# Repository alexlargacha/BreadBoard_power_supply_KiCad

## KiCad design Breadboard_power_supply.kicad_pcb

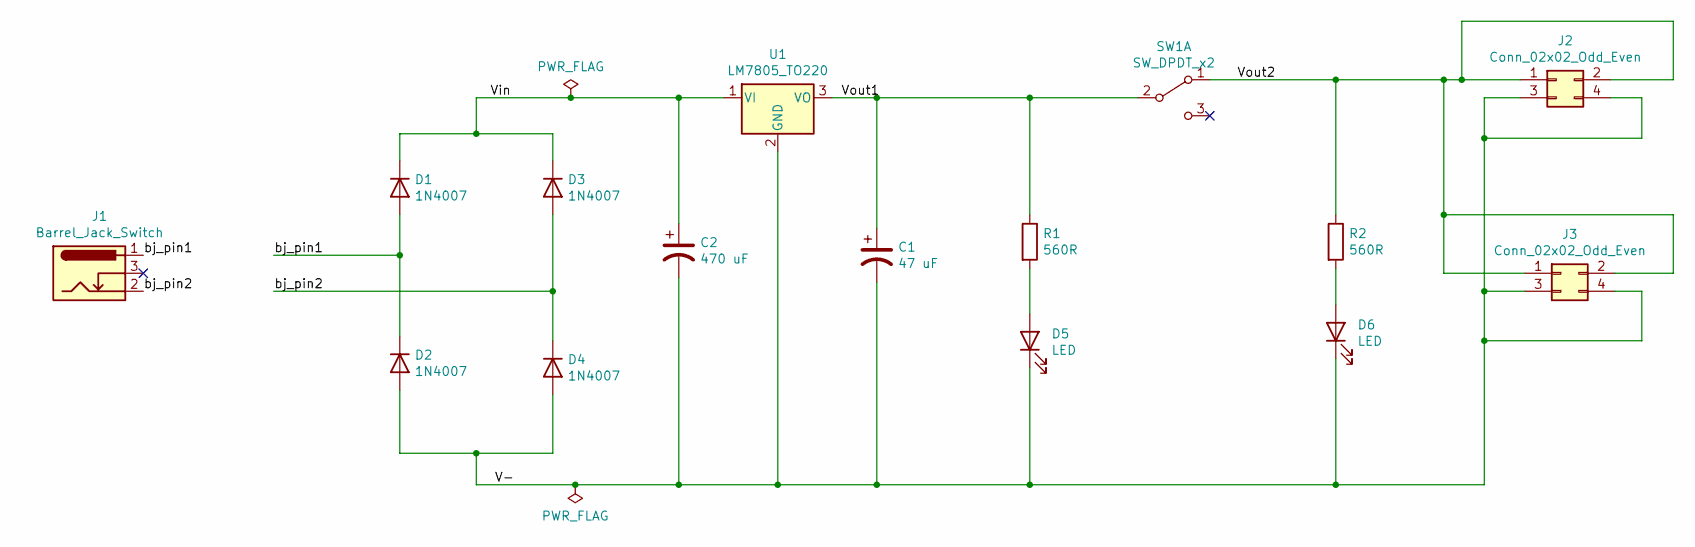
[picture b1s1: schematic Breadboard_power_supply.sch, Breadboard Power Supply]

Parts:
C1: 47 uF; CP_Radial_D6.3mm_P2.50mm
C2: 470 uF; CP_Radial_D10.0mm_P5.00mm
D1, D2, D3, D4: 1N4007; D_DO-41_SOD81_P10.16mm_Horizontal
D5, D6: LED; LED_D5.0mm
J1: Barrel_Jack_Switch; BarrelJack_CUI_PJ-102AH_Horizontal
J2, J3: Conn_02x02_Odd_Even; PinHeader_2x02_P2.54mm_Vertical
R1, R2: 560R; R_Axial_DIN0207_L6.3mm_D2.5mm_P7.62mm_Horizontal
SW1: SW_DPDT_x2; Switch_Slide_11.6x4mm_EG1218
U1: LM7805_TO220; TO-220-3_Vertical

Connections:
/V-: C1.2, C2.2, D2.2 (A), D4.2 (A), D5.1 (K), D6.1 (K), J2.3, J2.4, J3.3, J3.4, U1.2 (GND)
/Vin: C2.1, D1.1 (K), D3.1 (K), U1.1 (VI)
/Vout1: C1.1, R1.1, SW1.2 (B), U1.3 (VO)
/Vout2: J2.1, J2.2, J3.1, J3.2, R2.1, SW1.1 (A)
/bj_pin1: D1.2 (A), D2.1 (K), J1.1
/bj_pin2: D3.2 (A), D4.1 (K), J1.2
unnamed: D5.2 (A), R1.2
unnamed: D6.2 (A), R2.2

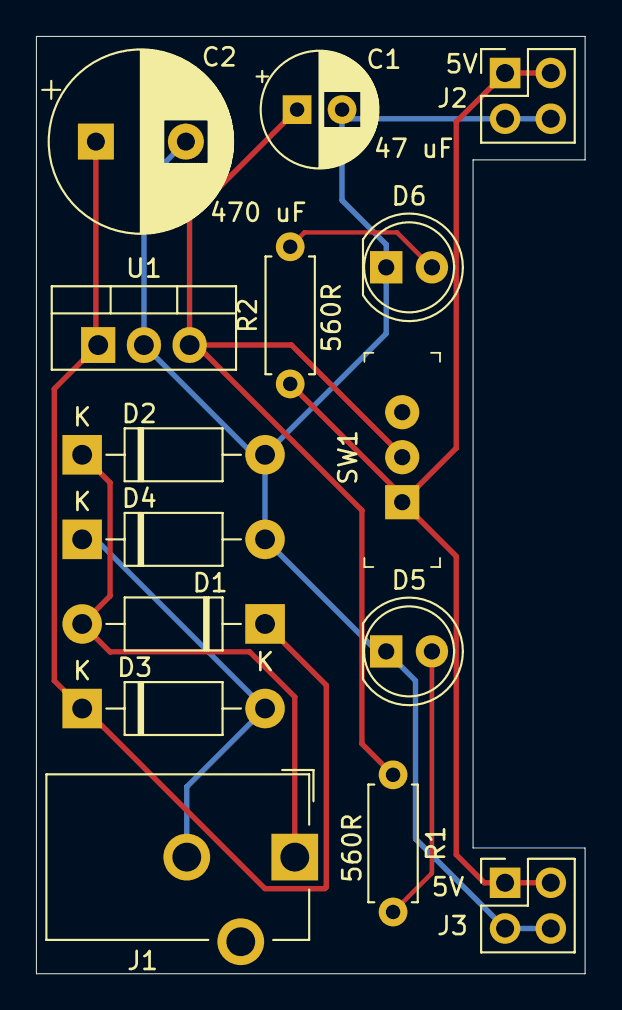
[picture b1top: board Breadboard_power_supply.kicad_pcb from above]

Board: 2 copper layers, 30.5 x 52.1 mm, 15 parts (0 on the bottom side), 8 nets.
